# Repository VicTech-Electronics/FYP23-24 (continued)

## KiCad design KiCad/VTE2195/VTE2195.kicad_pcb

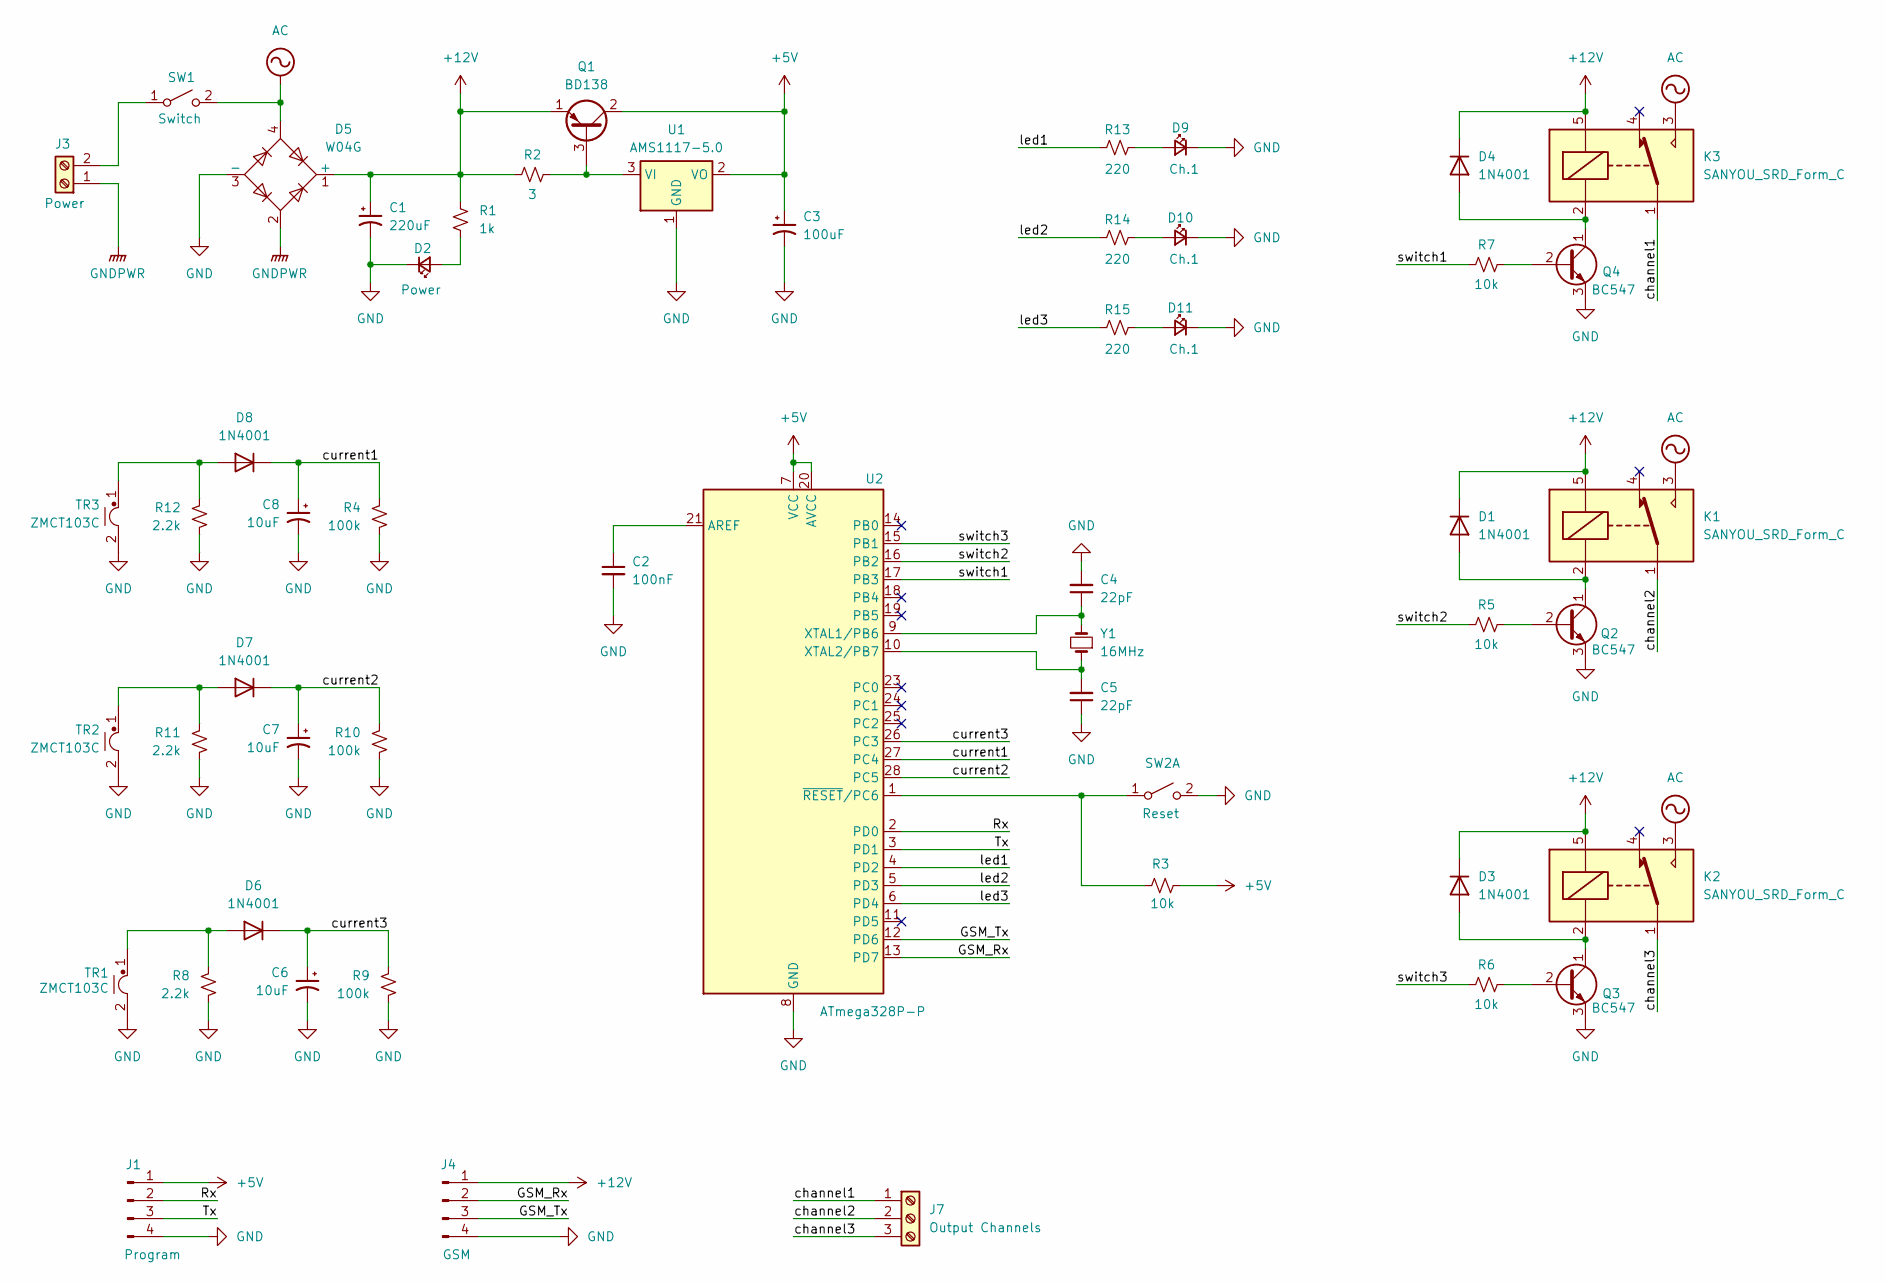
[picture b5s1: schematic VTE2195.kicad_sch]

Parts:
C1: 220uF; CP_Radial_D5.0mm_P2.50mm
C2: 100nF; C_Disc_D3.0mm_W1.6mm_P2.50mm
C3: 100uF; CP_Radial_D5.0mm_P2.50mm
C4, C5: 22pF; C_Disc_D3.0mm_W1.6mm_P2.50mm
C6, C7, C8: 10uF; CP_Radial_D5.0mm_P2.50mm
D1, D3, D4, D6, D7, D8: 1N4001; D_DO-41_SOD81_P10.16mm_Horizontal
D2: Power; LED_D3.0mm
D5: W04G; Diode_Bridge_Round_D9.8mm
D9, D10, D11: Ch.1; LED_D3.0mm
J1: Program; PinHeader_1x04_P2.54mm_Vertical
J3: Power; TerminalBlock_bornier-2_P5.08mm
J4: GSM; PinHeader_1x04_P2.54mm_Vertical
J7: Output Channels; TerminalBlock_bornier-3_P5.08mm
K1, K2, K3: SANYOU_SRD_Form_C; Relay_SPDT_SANYOU_SRD_Series_Form_C
Q1: BD138; TO-126-3_Vertical
Q2, Q3, Q4: BC547; TO-92_Inline
R1: 1k; R_Axial_DIN0207_L6.3mm_D2.5mm_P10.16mm_Horizontal
R2: 3; R_Axial_DIN0207_L6.3mm_D2.5mm_P10.16mm_Horizontal
R3, R5, R6, R7: 10k; R_Axial_DIN0207_L6.3mm_D2.5mm_P10.16mm_Horizontal
R4, R9, R10: 100k; R_Axial_DIN0207_L6.3mm_D2.5mm_P10.16mm_Horizontal
R8, R11, R12: 2.2k; R_Axial_DIN0207_L6.3mm_D2.5mm_P10.16mm_Horizontal
R13, R14, R15: 220; R_Axial_DIN0207_L6.3mm_D2.5mm_P10.16mm_Horizontal
SW1: Switch; TestPoint_2Pads_Pitch2.54mm_Drill0.8mm
SW2: Reset; SW_PUSH_6mm
TR1, TR2, TR3: ZMCT103C; Transformer_Zeming_ZMCT103C
U1: AMS1117-5.0; SOT-223-3_TabPin2
U2: ATmega328P-P; DIP-28_W7.62mm_Socket_LongPads
Y1: 16MHz; Crystal_HC50_Vertical

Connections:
+5V: C3.1, J1.1, Q1.2 (C), R3.2, U1.2 (VO), U2.7 (VCC), U2.20 (AVCC)
+12V: C1.1, D1.1 (K), D3.1 (K), D4.1 (K), D5.1 (+), J4.1, K1.5, K2.5, K3.5, Q1.1 (E), R1.1, R2.1
/GSM_Rx: J4.2, U2.13 (PD7)
/GSM_Tx: J4.3, U2.12 (PD6)
/Rx: J1.2, U2.2 (PD0)
/Tx: J1.3, U2.3 (PD1)
/channel1: J7.1, K3.1
/channel2: J7.2, K1.1
/channel3: J7.3, K2.1
/current1: C8.1, D8.1 (K), R4.1, U2.27 (PC4)
/current2: C7.1, D7.1 (K), R10.1, U2.28 (PC5)
/current3: C6.1, D6.1 (K), R9.1, U2.26 (PC3)
/led1: R13.1, U2.4 (PD2)
/led2: R14.1, U2.5 (PD3)
/led3: R15.1, U2.6 (PD4)
/switch1: R7.1, U2.17 (PB3)
/switch2: R5.1, U2.16 (PB2)
/switch3: R6.1, U2.15 (PB1)
AC: D5.4, K1.3, K2.3, K3.3, SW1.2 (B)
GND: C1.2, C2.2, C3.2, C4.2, C5.1, C6.2, C7.2, C8.2, D2.1 (K), D5.3 (-), D9.1 (K), D10.1 (K), D11.1 (K), J1.4, J4.4, Q2.3 (E), Q3.3 (E), Q4.3 (E), R4.2, R8.2, R9.2, R10.2, R11.2, R12.2, SW2.2 (B), TR1.2, TR2.2, TR3.2, U1.1 (GND), U2.8 (GND), U2.22 (GND)
GNDPWR: D5.2, J3.1
unnamed: D1.2 (A), K1.2, Q2.1 (C)
unnamed: D2.2 (A), R1.2
unnamed: D3.2 (A), K2.2, Q3.1 (C)
unnamed: D4.2 (A), K3.2, Q4.1 (C)
unnamed: D6.2 (A), R8.1, TR1.1
unnamed: D7.2 (A), R11.1, TR2.1
unnamed: D8.2 (A), R12.1, TR3.1
unnamed: D9.2 (A), R13.2
unnamed: D10.2 (A), R14.2
unnamed: D11.2 (A), R15.2
unnamed: J3.2, SW1.1 (A)
unnamed: Q1.3 (B), R2.2, U1.3 (VI)
unnamed: Q2.2 (B), R5.2
unnamed: Q3.2 (B), R6.2
unnamed: Q4.2 (B), R7.2
unnamed: R3.1, SW2.1 (A), U2.1 (~RESET/PC6)
unnamed: C2.1, U2.21 (AREF)
unnamed: C4.1, U2.9 (XTAL1/PB6), Y1.2
unnamed: C5.2, U2.10 (XTAL2/PB7), Y1.1

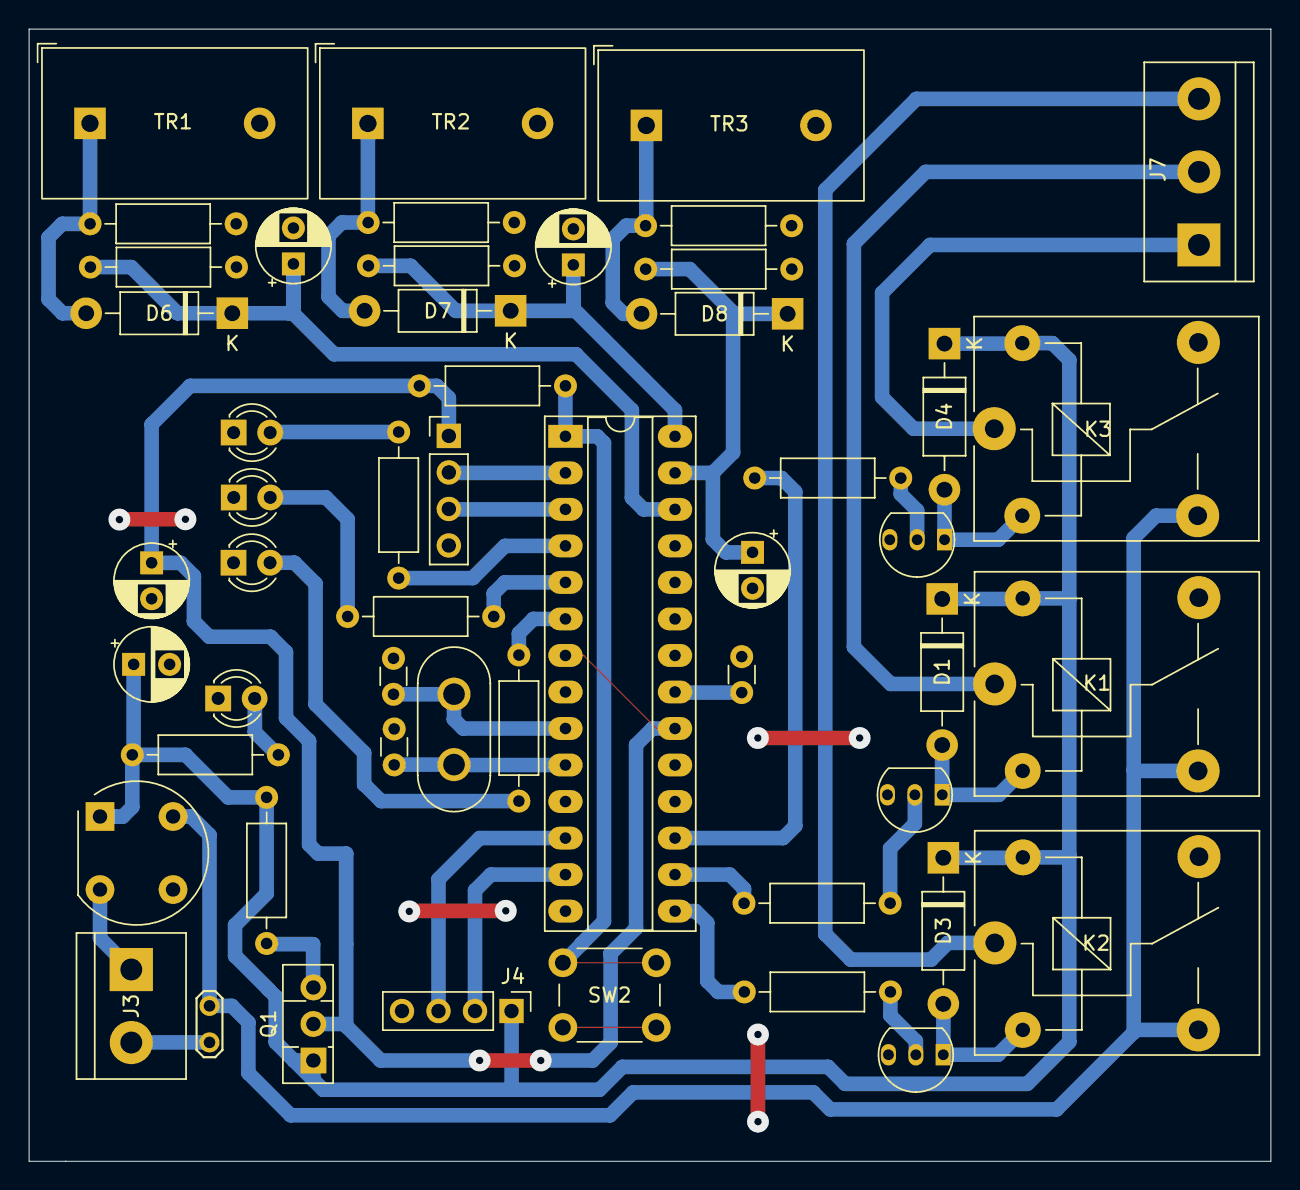
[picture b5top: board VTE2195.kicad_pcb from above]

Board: 2 copper layers, 86.4 x 78.7 mm, 53 parts (1 on the bottom side), 40 nets.

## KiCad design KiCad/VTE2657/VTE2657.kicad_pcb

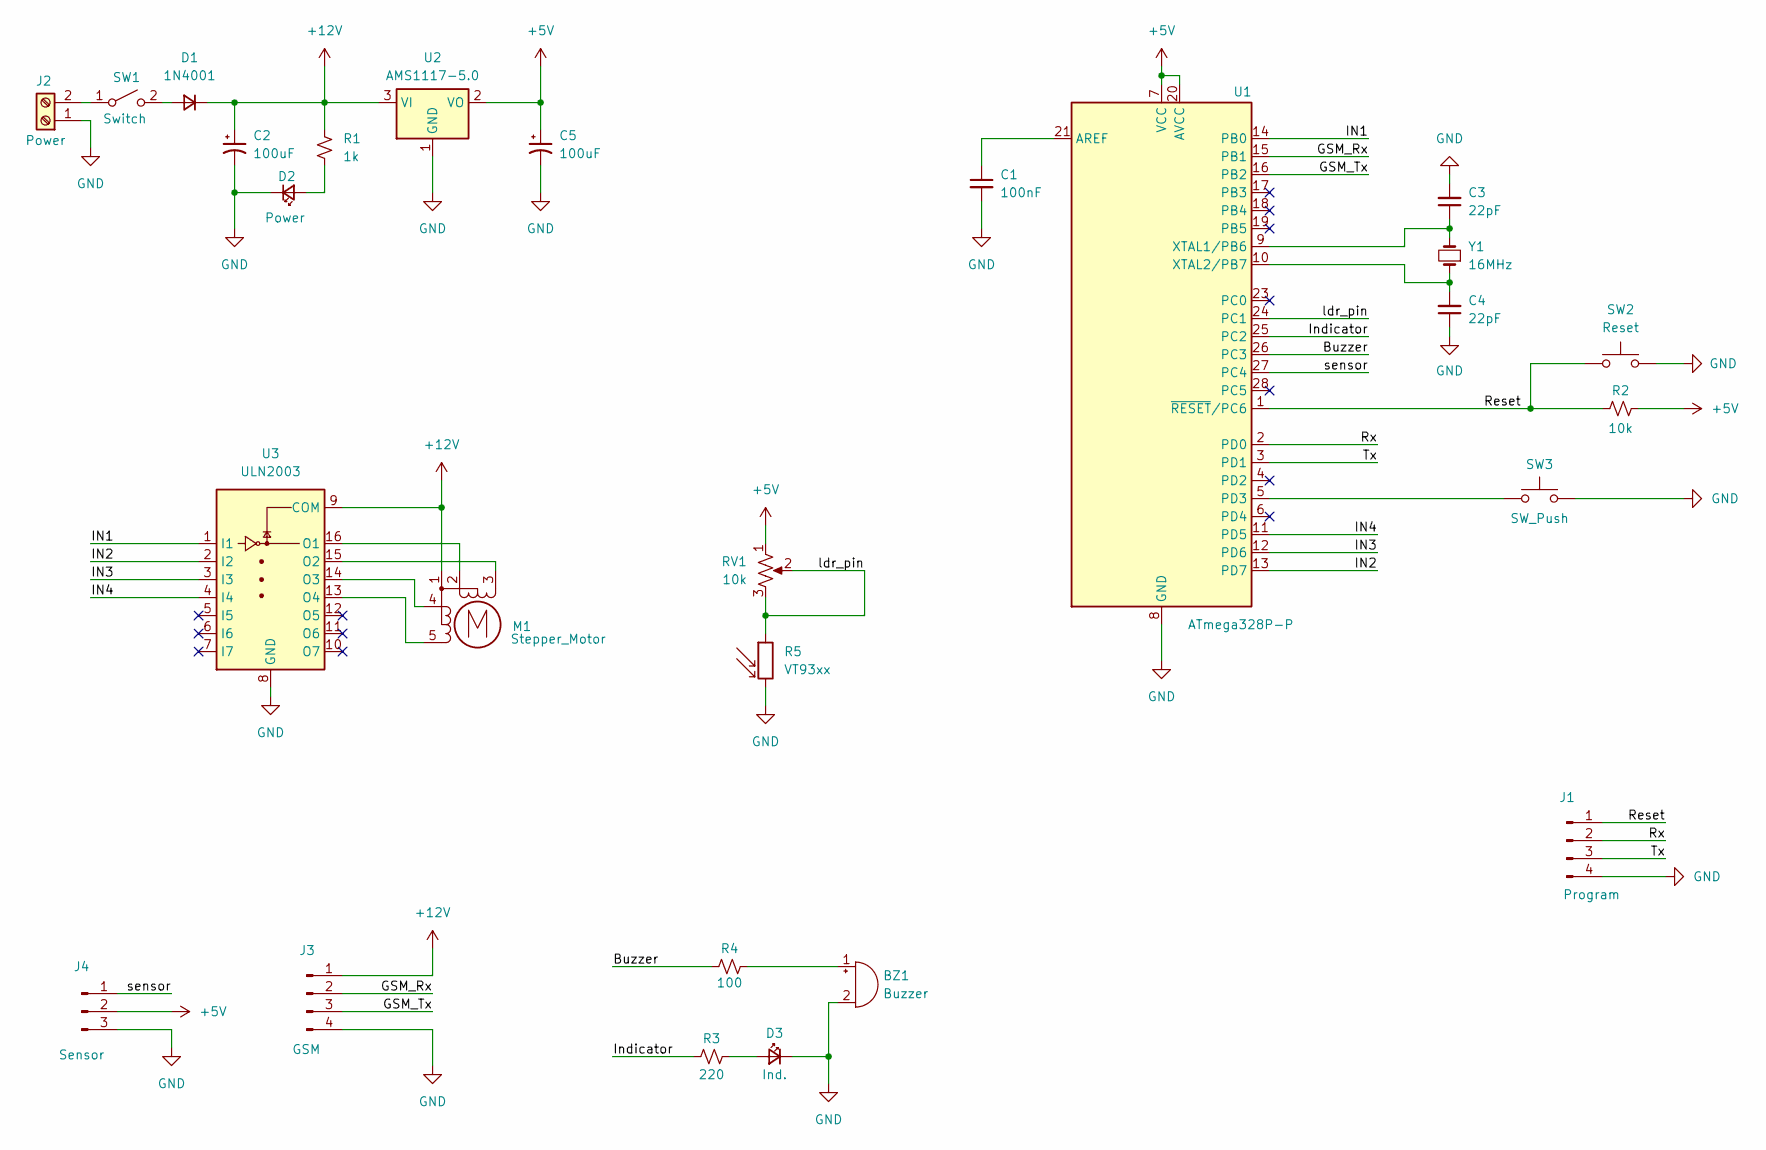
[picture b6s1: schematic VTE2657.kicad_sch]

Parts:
BZ1: Buzzer; Buzzer_12x9.5RM7.6
C1: 100nF; C_Disc_D3.0mm_W1.6mm_P2.50mm
C2, C5: 100uF; CP_Radial_D5.0mm_P2.50mm
C3, C4: 22pF; C_Disc_D3.0mm_W1.6mm_P2.50mm
D1: 1N4001; D_A-405_P10.16mm_Horizontal
D2: Power; LED_D3.0mm
D3: Ind.; LED_D3.0mm
J1: Program; PinHeader_1x04_P2.54mm_Vertical
J2: Power; TerminalBlock_bornier-2_P5.08mm
J3: GSM; PinHeader_1x04_P2.54mm_Vertical
J4: Sensor; PinHeader_1x03_P2.54mm_Vertical
M1: Stepper_Motor; PinHeader_1x05_P2.54mm_Vertical
R1: 1k; R_Axial_DIN0207_L6.3mm_D2.5mm_P10.16mm_Horizontal
R2: 10k; R_Axial_DIN0207_L6.3mm_D2.5mm_P10.16mm_Horizontal
R3: 220; R_Axial_DIN0207_L6.3mm_D2.5mm_P10.16mm_Horizontal
R4: 100; R_Axial_DIN0207_L6.3mm_D2.5mm_P10.16mm_Horizontal
R5: VT93xx; R_LDR_4.9x4.2mm_P2.54mm_Vertical
RV1: 10k; Potentiometer_Runtron_RM-065_Vertical
SW1: Switch; TestPoint_2Pads_Pitch2.54mm_Drill0.8mm
SW2: Reset; SW_PUSH_6mm
SW3: SW_Push; TestPoint_2Pads_Pitch2.54mm_Drill0.8mm
U1: ATmega328P-P; DIP-28_W7.62mm_Socket_LongPads
U2: AMS1117-5.0; SOT-223-3_TabPin2
U3: ULN2003; DIP-16_W7.62mm_LongPads
Y1: 16MHz; Crystal_HC50_Vertical

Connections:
+5V: C5.1, J4.2, R2.2, RV1.1, U1.7 (VCC), U1.20 (AVCC), U2.2 (VO)
+12V: C2.1, D1.1 (K), J3.1, M1.1, R1.1, U2.3 (VI), U3.9 (COM)
/Buzzer: R4.1, U1.26 (PC3)
/GSM_Rx: J3.2, U1.15 (PB1)
/GSM_Tx: J3.3, U1.16 (PB2)
/IN1: U1.14 (PB0), U3.1 (I1)
/IN2: U1.13 (PD7), U3.2 (I2)
/IN3: U1.12 (PD6), U3.3 (I3)
/IN4: U1.11 (PD5), U3.4 (I4)
/Indicator: R3.1, U1.25 (PC2)
/Reset: J1.1, R2.1, SW2.1, U1.1 (~RESET/PC6)
/Rx: J1.2, U1.2 (PD0)
/Tx: J1.3, U1.3 (PD1)
/ldr_pin: R5.1, RV1.2, RV1.3, U1.24 (PC1)
/sensor: J4.1, U1.27 (PC4)
GND: BZ1.2 (-), C1.2, C2.2, C3.2, C4.1, C5.2, D2.1 (K), D3.1 (K), J1.4, J2.1, J3.4, J4.3, R5.2, SW2.2, SW3.1, U1.8 (GND), U1.22 (GND), U2.1 (GND), U3.8 (GND)
unnamed: BZ1.1 (+), R4.2
unnamed: D1.2 (A), SW1.2 (B)
unnamed: D2.2 (A), R1.2
unnamed: D3.2 (A), R3.2
unnamed: J2.2, SW1.1 (A)
unnamed: M1.3 (-), U3.15 (O2)
unnamed: C1.1, U1.21 (AREF)
unnamed: SW3.2, U1.5 (PD3)
unnamed: C3.1, U1.9 (XTAL1/PB6), Y1.2
unnamed: C4.2, U1.10 (XTAL2/PB7), Y1.1
unnamed: M1.2, U3.16 (O1)
unnamed: M1.4, U3.14 (O3)
unnamed: M1.5, U3.13 (O4)

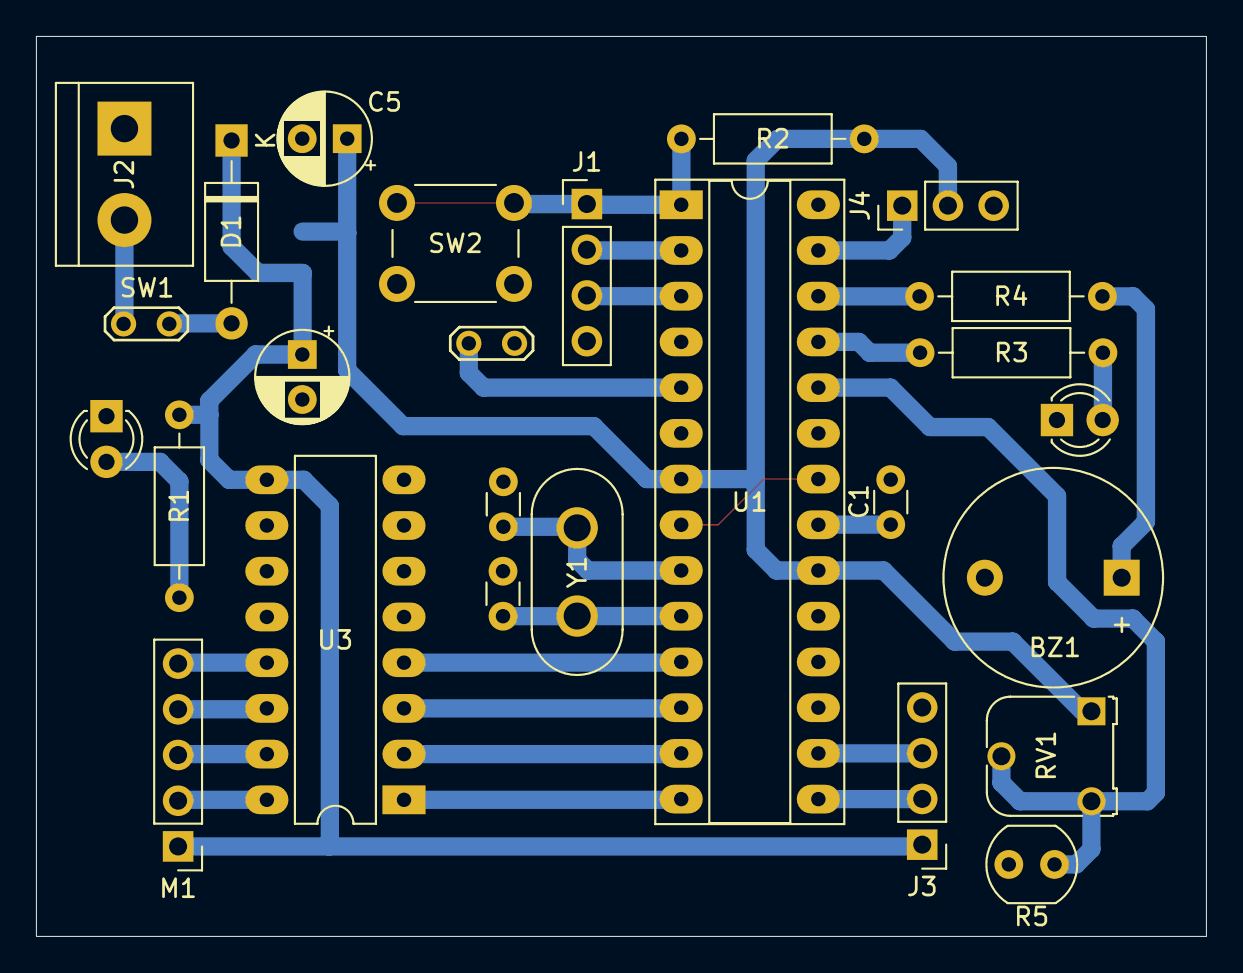
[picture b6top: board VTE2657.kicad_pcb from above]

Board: 2 copper layers, 65.0 x 50.0 mm, 27 parts (1 on the bottom side), 29 nets.

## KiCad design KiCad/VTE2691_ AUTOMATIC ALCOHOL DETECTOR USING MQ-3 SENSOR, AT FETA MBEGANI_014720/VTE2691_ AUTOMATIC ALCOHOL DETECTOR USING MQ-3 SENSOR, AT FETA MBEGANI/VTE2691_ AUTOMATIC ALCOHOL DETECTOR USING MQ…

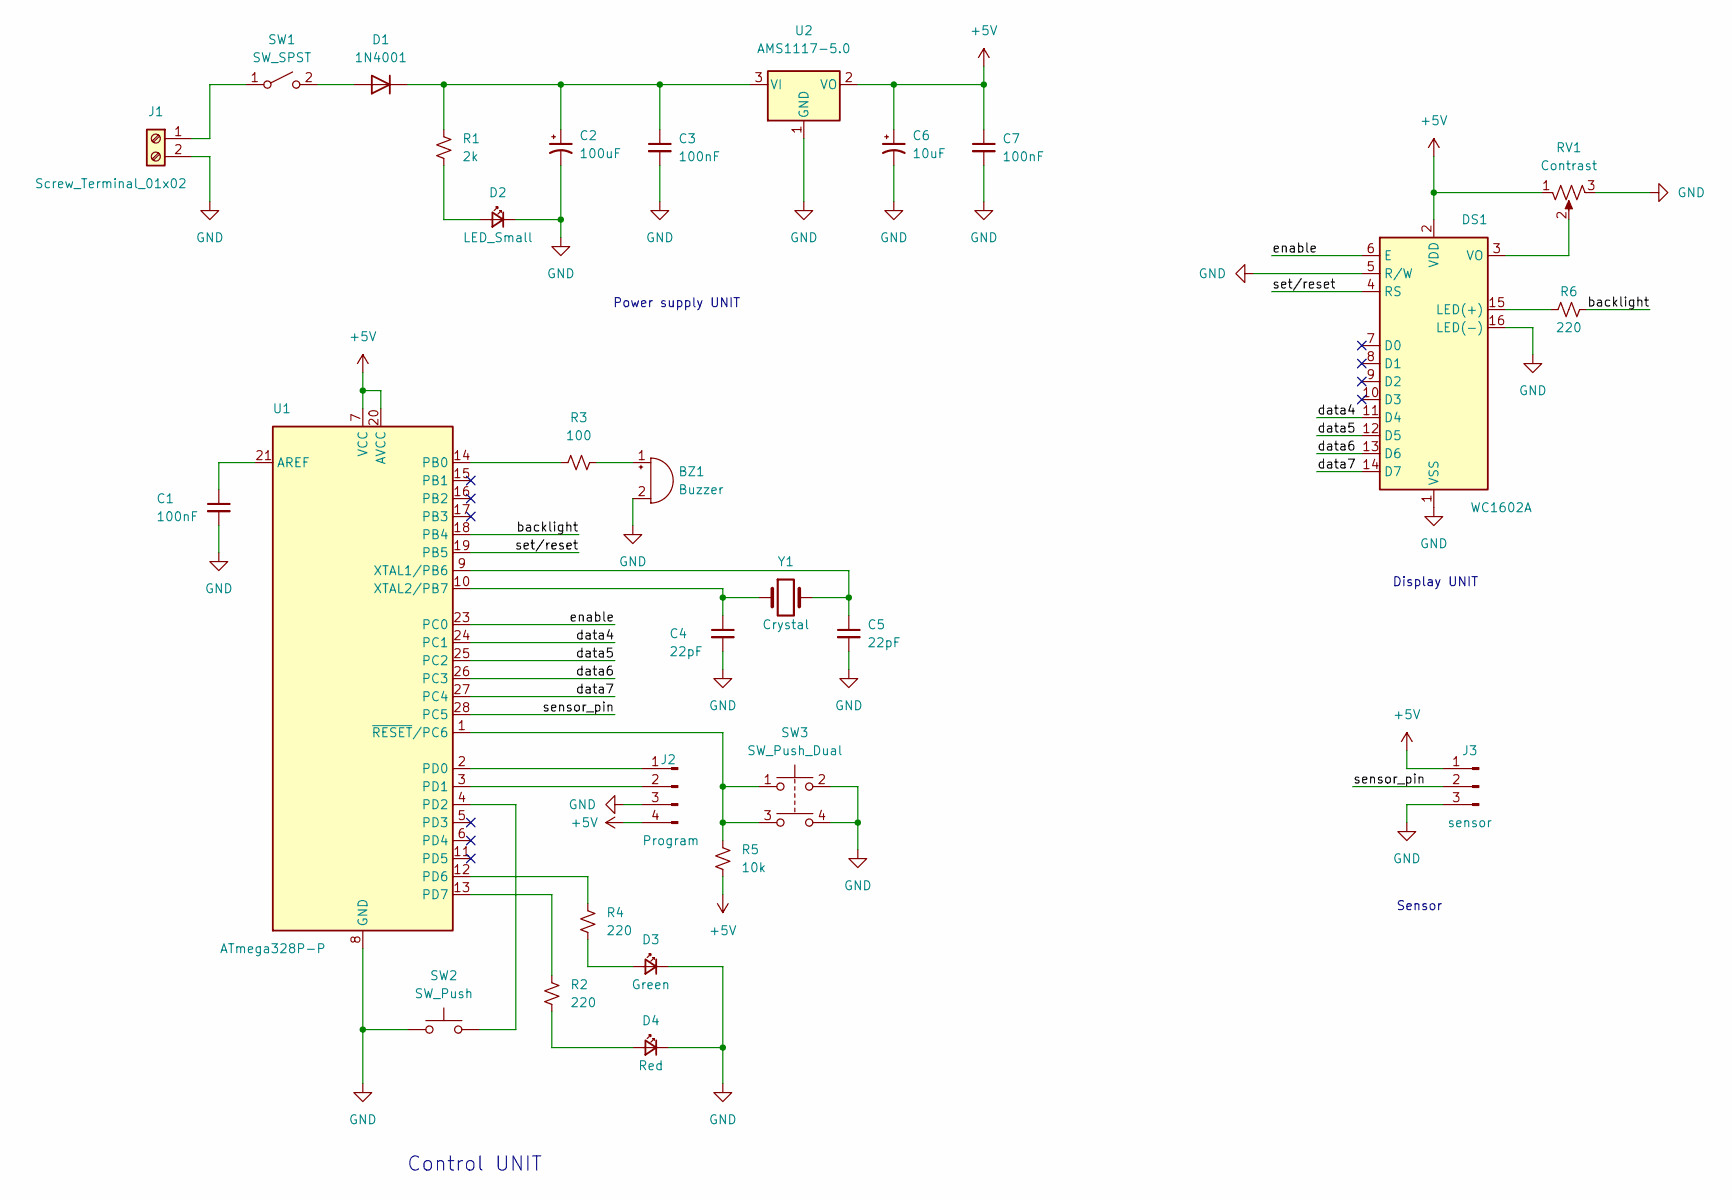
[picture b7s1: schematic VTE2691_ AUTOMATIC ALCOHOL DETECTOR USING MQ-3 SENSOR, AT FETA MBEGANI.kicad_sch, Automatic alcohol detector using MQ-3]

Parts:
BZ1: Buzzer; Buzzer_12x9.5RM7.6
C1, C3, C7: 100nF; C_Disc_D3.0mm_W1.6mm_P2.50mm
C2: 100uF; CP_Radial_D5.0mm_P2.50mm
C4, C5: 22pF; C_Disc_D3.0mm_W1.6mm_P2.50mm
C6: 10uF; CP_Radial_D5.0mm_P2.50mm
D1: 1N4001; D_DO-41_SOD81_P10.16mm_Horizontal
D2: LED_Small; LED_D3.0mm_Clear
D3: Green; LED_D3.0mm_Clear
D4: Red; LED_D3.0mm_Clear
DS1: WC1602A
J1: Screw_Terminal_01x02; TerminalBlock_bornier-2_P5.08mm
J2: Program; PinHeader_1x04_P2.54mm_Vertical
J3: sensor; PinHeader_1x03_P2.54mm_Vertical
R1: 2k; R_Axial_DIN0207_L6.3mm_D2.5mm_P10.16mm_Horizontal
R2, R4, R6: 220; R_Axial_DIN0207_L6.3mm_D2.5mm_P10.16mm_Horizontal
R3: 100; R_Axial_DIN0207_L6.3mm_D2.5mm_P10.16mm_Horizontal
R5: 10k; R_Axial_DIN0207_L6.3mm_D2.5mm_P10.16mm_Horizontal
RV1: Contrast; Potentiometer_Runtron_RM-065_Vertical
SW1: SW_SPST; PinHeader_2x01_P2.54mm_Vertical
SW2: SW_Push; PinHeader_2x01_P2.54mm_Vertical
SW3: SW_Push_Dual; SW_TH_Tactile_Omron_B3F-10xx
U1: ATmega328P-P; DIP-28_W7.62mm_Socket_LongPads
U2: AMS1117-5.0; SOT-223-3_TabPin2
Y1: Crystal; Crystal_HC18-U_Vertical

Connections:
+5V: C6.1, C7.1, DS1.2 (VDD), J2.4, J3.1, R5.2, RV1.1, U1.7 (VCC), U1.20 (AVCC), U2.2 (VO)
/backlight: R6.2, U1.18 (PB4)
/data4: DS1.11 (D4), U1.24 (PC1)
/data5: DS1.12 (D5), U1.25 (PC2)
/data6: DS1.13 (D6), U1.26 (PC3)
/data7: DS1.14 (D7), U1.27 (PC4)
/enable: DS1.6 (E), U1.23 (PC0)
/sensor_pin: J3.2, U1.28 (PC5)
/set/reset: DS1.4 (RS), U1.19 (PB5)
GND: BZ1.2 (+), C1.2, C2.2, C3.2, C4.2, C5.2, C6.2, C7.2, D2.1 (K), D3.1 (K), D4.1 (K), DS1.1 (VSS), DS1.5 (R/W), DS1.16 (LED(-)), J1.2, J2.3, J3.3, RV1.3, SW2.1, SW3.2, SW3.4, U1.8 (GND), U1.22 (GND), U2.1 (GND)
unnamed: BZ1.1 (-), R3.2
unnamed: C1.1, U1.21 (AREF)
unnamed: C2.1, C3.1, D1.1 (K), R1.1, U2.3 (VI)
unnamed: C4.1, U1.10 (XTAL2/PB7), Y1.1
unnamed: C5.1, U1.9 (XTAL1/PB6), Y1.2
unnamed: D1.2 (A), SW1.2 (B)
unnamed: D2.2 (A), R1.2
unnamed: D3.2 (A), R4.2
unnamed: D4.2 (A), R2.2
unnamed: DS1.3 (VO), RV1.2
unnamed: DS1.15 (LED(+)), R6.1
unnamed: J1.1, SW1.1 (A)
unnamed: J2.1, U1.2 (PD0)
unnamed: J2.2, U1.3 (PD1)
unnamed: R2.1, U1.13 (PD7)
unnamed: R3.1, U1.14 (PB0)
unnamed: R4.1, U1.12 (PD6)
unnamed: R5.1, SW3.1, SW3.3, U1.1 (~RESET/PC6)
unnamed: SW2.2, U1.4 (PD2)

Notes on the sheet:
Sensor
Display UNIT
Power supply UNIT
Control UNIT

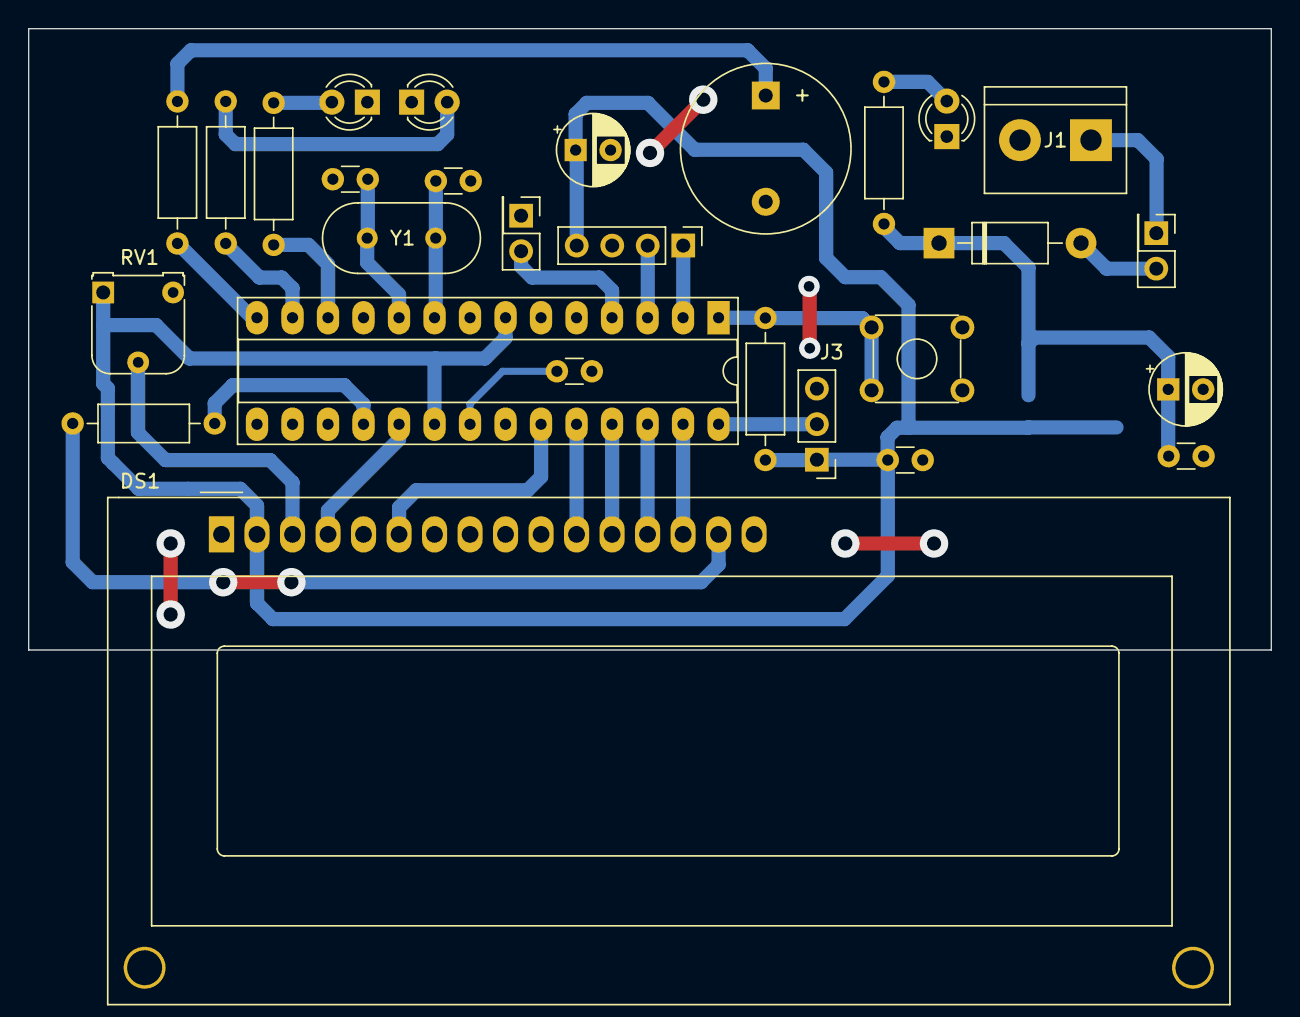
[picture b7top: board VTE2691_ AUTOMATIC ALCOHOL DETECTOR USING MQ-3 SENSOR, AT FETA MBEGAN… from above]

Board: 2 copper layers, 88.9 x 44.5 mm, 29 parts (1 on the bottom side), 29 nets.

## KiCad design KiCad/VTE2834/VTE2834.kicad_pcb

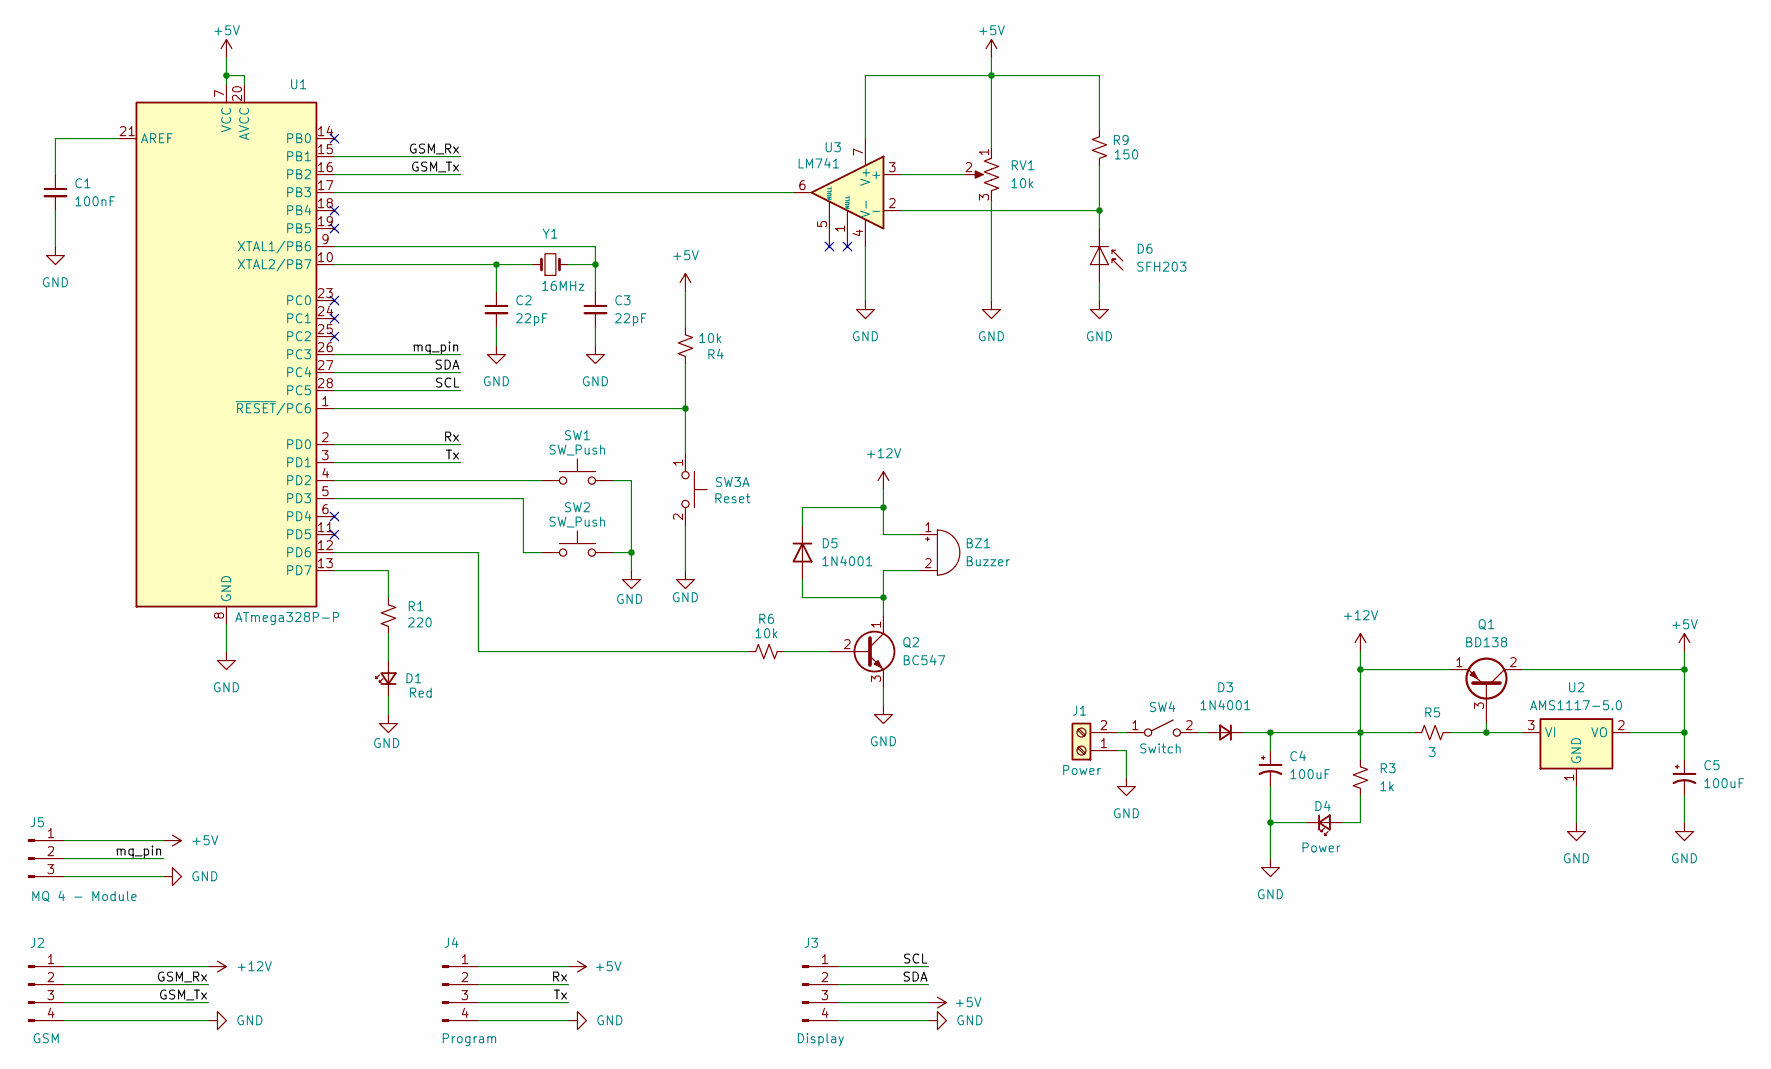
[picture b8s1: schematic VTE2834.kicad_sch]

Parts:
BZ1: Buzzer; PinHeader_1x02_P2.54mm_Vertical
C1: 100nF; C_Disc_D3.0mm_W1.6mm_P2.50mm
C2, C3: 22pF; C_Disc_D3.0mm_W1.6mm_P2.50mm
C4, C5: 100uF; CP_Radial_D5.0mm_P2.50mm
D1: Red; LED_D3.0mm_Clear
D3: 1N4001; D_A-405_P10.16mm_Horizontal
D4: Power; LED_D3.0mm
D5: 1N4001; D_DO-41_SOD81_P10.16mm_Horizontal
D6: SFH203; LED_D5.0mm_IRGrey
J1: Power; TerminalBlock_bornier-2_P5.08mm
J2: GSM; PinHeader_1x04_P2.54mm_Vertical
J3: Display; PinHeader_1x04_P2.54mm_Vertical
J4: Program; PinHeader_1x04_P2.54mm_Vertical
J5: MQ 4 - Module; PinHeader_1x03_P2.54mm_Vertical
Q1: BD138; TO-126-3_Vertical
Q2: BC547; TO-92_Inline
R1: 220; R_Axial_DIN0207_L6.3mm_D2.5mm_P10.16mm_Horizontal
R3: 1k; R_Axial_DIN0207_L6.3mm_D2.5mm_P10.16mm_Horizontal
R4, R6: 10k; R_Axial_DIN0207_L6.3mm_D2.5mm_P10.16mm_Horizontal
R5: 3; R_Axial_DIN0207_L6.3mm_D2.5mm_P10.16mm_Horizontal
R9: 150; R_Axial_DIN0207_L6.3mm_D2.5mm_P10.16mm_Horizontal
RV1: 10k; Potentiometer_Runtron_RM-065_Vertical
SW1, SW2: SW_Push; PinHeader_2x01_P2.00mm_Vertical
SW3: Reset; SW_PUSH_6mm_H4.3mm
SW4: Switch; TestPoint_2Pads_Pitch2.54mm_Drill0.8mm
U1: ATmega328P-P; DIP-28_W7.62mm
U2: AMS1117-5.0; SOT-223-3_TabPin2
U3: LM741; DIP-8_W7.62mm_LongPads
Y1: 16MHz; Crystal_HC18-U_Vertical

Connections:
+5V: C5.1, J3.3, J4.1, J5.1, Q1.2 (C), R4.2, R9.2, RV1.1, U1.7 (VCC), U1.20 (AVCC), U2.2 (VO), U3.7 (V+)
+12V: BZ1.1 (+), C4.1, D3.1 (K), D5.1 (K), J2.1, Q1.1 (E), R3.1, R5.1
/GSM_Rx: J2.2, U1.15 (PB1)
/GSM_Tx: J2.3, U1.16 (PB2)
/Rx: J4.2, U1.2 (PD0)
/SCL: J3.1, U1.28 (PC5)
/SDA: J3.2, U1.27 (PC4)
/Tx: J4.3, U1.3 (PD1)
/mq_pin: J5.2, U1.26 (PC3)
GND: C1.2, C2.2, C3.2, C4.2, C5.2, D1.1 (K), D4.1 (K), D6.2 (A), J1.1, J2.4, J3.4, J4.4, J5.3, Q2.3 (E), RV1.3, SW1.2, SW2.2, SW3.2 (D), U1.8 (GND), U1.22 (GND), U2.1 (GND), U3.4 (V-)
unnamed: BZ1.2 (-), D5.2 (A), Q2.1 (C)
unnamed: D1.2 (A), R1.2
unnamed: D3.2 (A), SW4.2 (B)
unnamed: D4.2 (A), R3.2
unnamed: D6.1 (K), R9.1, U3.2 (-)
unnamed: J1.2, SW4.1 (A)
unnamed: Q1.3 (B), R5.2, U2.3 (VI)
unnamed: Q2.2 (B), R6.2
unnamed: R4.1, SW3.1 (C), U1.1 (~RESET/PC6)
unnamed: C1.1, U1.21 (AREF)
unnamed: U1.17 (PB3), U3.6
unnamed: SW1.1, U1.4 (PD2)
unnamed: SW2.1, U1.5 (PD3)
unnamed: R6.1, U1.12 (PD6)
unnamed: R1.1, U1.13 (PD7)
unnamed: C3.1, U1.9 (XTAL1/PB6), Y1.2
unnamed: C2.1, U1.10 (XTAL2/PB7), Y1.1
unnamed: RV1.2, U3.3 (+)

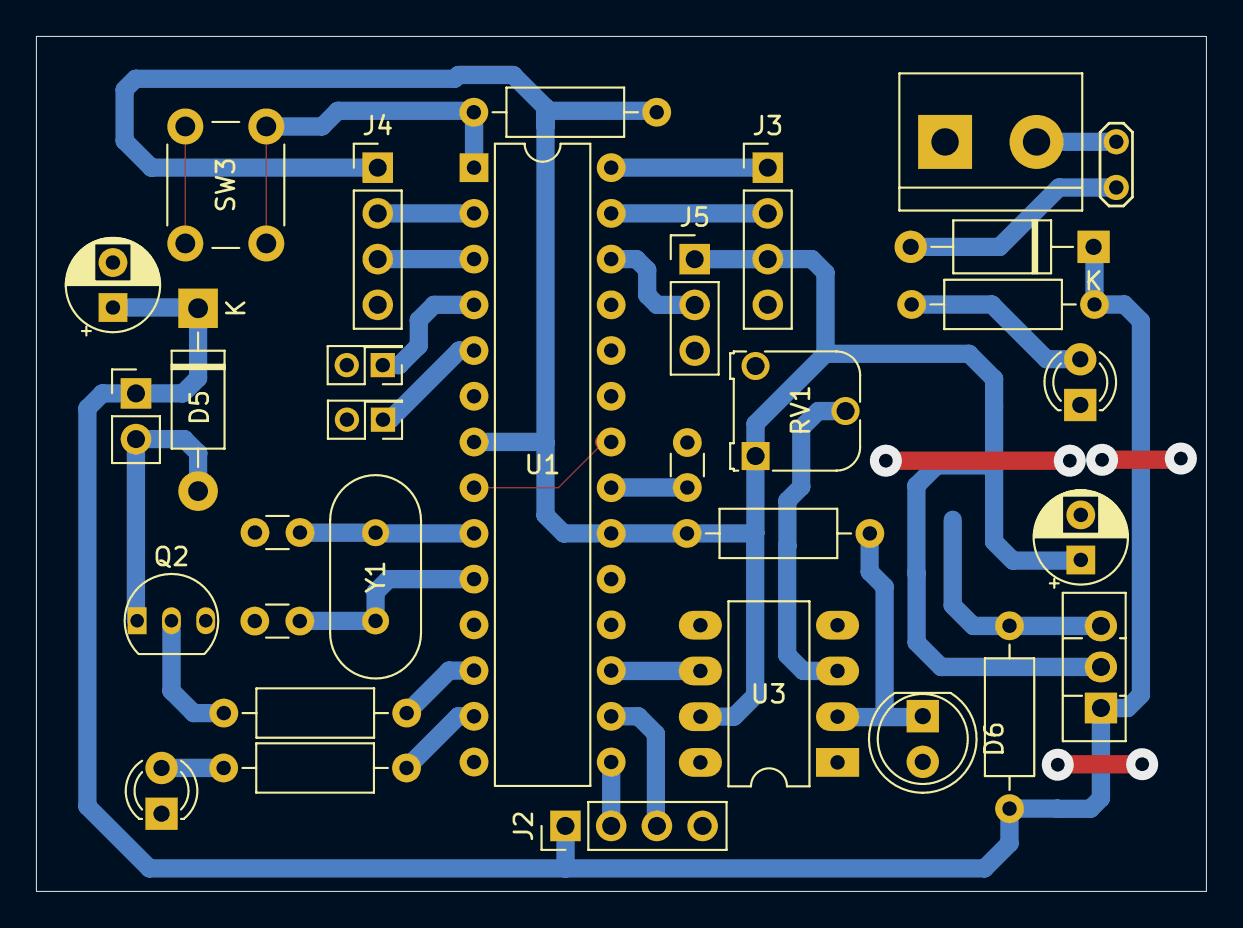
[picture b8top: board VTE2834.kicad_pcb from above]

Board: 2 copper layers, 65.0 x 47.5 mm, 33 parts (1 on the bottom side), 28 nets.
